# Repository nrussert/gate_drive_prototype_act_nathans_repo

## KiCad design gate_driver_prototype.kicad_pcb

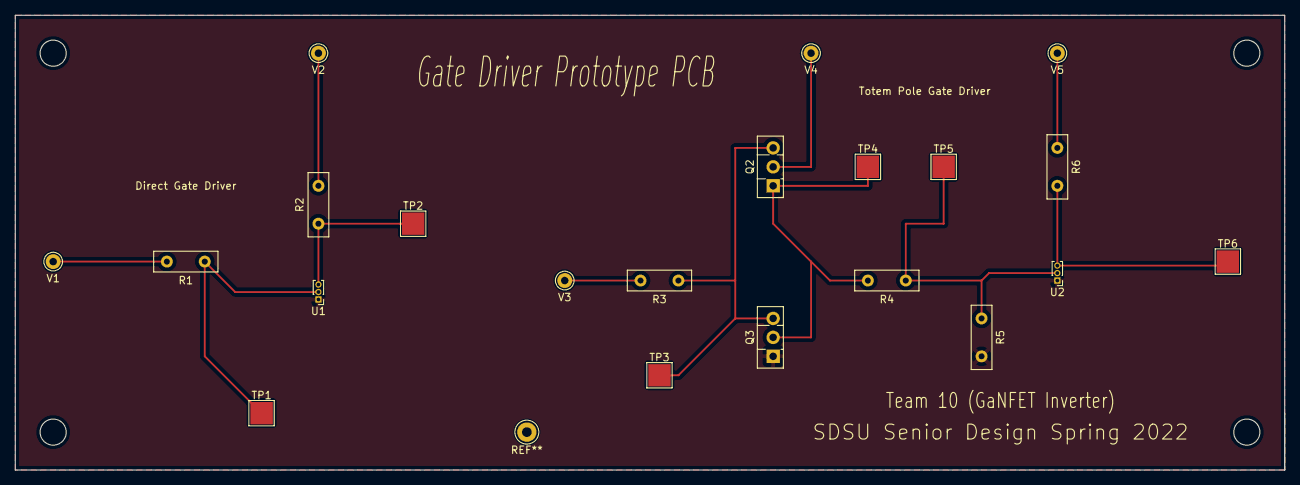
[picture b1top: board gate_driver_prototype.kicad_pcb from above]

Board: 2 copper layers, 170.2 x 61.0 mm, 21 parts (0 on the bottom side), 12 nets.

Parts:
Q2: BD435; TO-126-3_Vertical
Q3: BD436; TO-126-3_Vertical
R1, R2, R3, R4, R5, R6: R_US; R_Box_L8.4mm_W2.5mm_P5.08mm
TP1, TP2, TP3, TP4, TP5, TP6: TestPoint; TestPoint_Pad_3.0x3.0mm
U1, U2: GaNFET; PinHeader_1x03_P1.00mm_Vertical
V1: PWM-Direct; Pin_D1.0mm_L10.0mm
V2: V-Load-Direct; Pin_D1.0mm_L10.0mm
V3: PWM-Totem; Pin_D1.0mm_L10.0mm
V4: VSwitch; Pin_D1.0mm_L10.0mm
V5: V-Load-Totem; Pin_D1.0mm_L10.0mm

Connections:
GND: Q3.1 (E), R5.2, U1.1, U2.1
unnamed: Q2.1 (E), Q3.2 (C), R4.2, TP4.1
unnamed: Q2.2 (C), V4.1
unnamed: Q2.3 (B), Q3.3 (B), R3.1, TP3.1
unnamed: R1.1, TP1.1, U1.2
unnamed: R1.2, V1.1
unnamed: R2.2, V2.1
unnamed: R3.2, V3.1
unnamed: R4.1, R5.1, TP5.1, U2.2
unnamed: R6.1, V5.1
unnamed: R6.2, TP6.1, U2.3
unnamed: R2.1, TP2.1, U1.3

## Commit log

2022-04-07 inital commit of all my files
